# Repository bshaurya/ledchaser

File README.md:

# shauryachaser LED Chaser

a cricket-ball themed LED chaser because why not  
hardware-only, no firmware needed. Powered by a 555 + CD4017  
and mounted inside a shiny 3D-printed cricket ball enclosure

## What is this

Basically I wanted to make something fun, weird, and actually functional.  
So I built an LED chaser circuit (classic 555 + CD4017) and wrapped it inside  
a custom Fusion 360 modeled cricket ball enclosure with seam lines, stitching, and a full LED ring.

## Hardware

- **Logic**: NE555P (clock) + CD4017BE (decade counter)
- **LEDs**: 10x 5mm diffused LEDs arranged around the ball
- **Resistors**: 10x LED current limiters + timing resistors
- **Potentiometer**: 50k trim pot for speed control
- **Caps**: 1uF electrolytic + 0.01uF ceramic
- **Power**: Standard 5V input (2-pin header)
- **Enclosure**: 93mm diameter 3D-printed cricket ball with stitched seam

## How it works

- The **555 timer** generates a square wave clock (rate set by RV1).
- Every clock pulse goes into the **CD4017**, which advances to the next output: Q0 → Q1 → Q2 → ... → Q9 → loops back
- Each Q output drives an LED through a 470Ω resistor.
- Result = lights chase around the seam like a rotating/bouncing cricket ball.

You rotate RV1 to speed up or slow down the chase.

## BOM

**ICs**
- 1x NE555P (DIP-8)
- 1x CD4017BE (DIP-16)

**LEDs**
- 10x 5mm LEDs (any color)

**Resistors**
- 10x 470Ω (LEDs)
- 2x 1kΩ (timing)

**Potentiometer**
- 1x 50kΩ trim pot (3386P style)

**Capacitors**
- 1x 1uF electrolytic
- 1x 0.01uF ceramic

**Connectors**
- 1x 2-pin 2.54mm power header

**PCB**
- 1x Circular 93mm custom PCB (KiCad)

**Case**
- ~70–100g PLA (for the cricket ball halves)
- 4x M3x16 screws (optional if mounting)
- 4x M3 heatset inserts (optional)

## Estimated Prices

(approx retail), see BOM.csv

- LEDs: ~$1.00 for all 10  
- Resistors: ~$0.60  
- NE555P: ~$0.40  
- CD4017BE: ~$0.70  
- Potentiometer: ~$0.50  
- Capacitors: ~$0.25  
- Header: ~$0.10  
- PCB: ~$15 (JLCPCB)  
- PLA: ~$1 worth  
**Total:** ~**$20** all-in

## Building one

- `/ledcha` — KiCad PCB + schematic
- `/cad` — 3D Fusion 360 files for the cricket enclosure
- `/assets` — top/side/bottom views, schema and pcb
Steps:

1. Export Gerbers → order PCB from JLCPCB/Seeed/etc.
2. 3D print the cricket ball halves.
3. Solder the PCB: ICs, resistors, LEDs, pot, caps.
4. Insert the PCB inside the enclosure.
5. Power with 5V.
6. Rotate the pot to change chase speed.

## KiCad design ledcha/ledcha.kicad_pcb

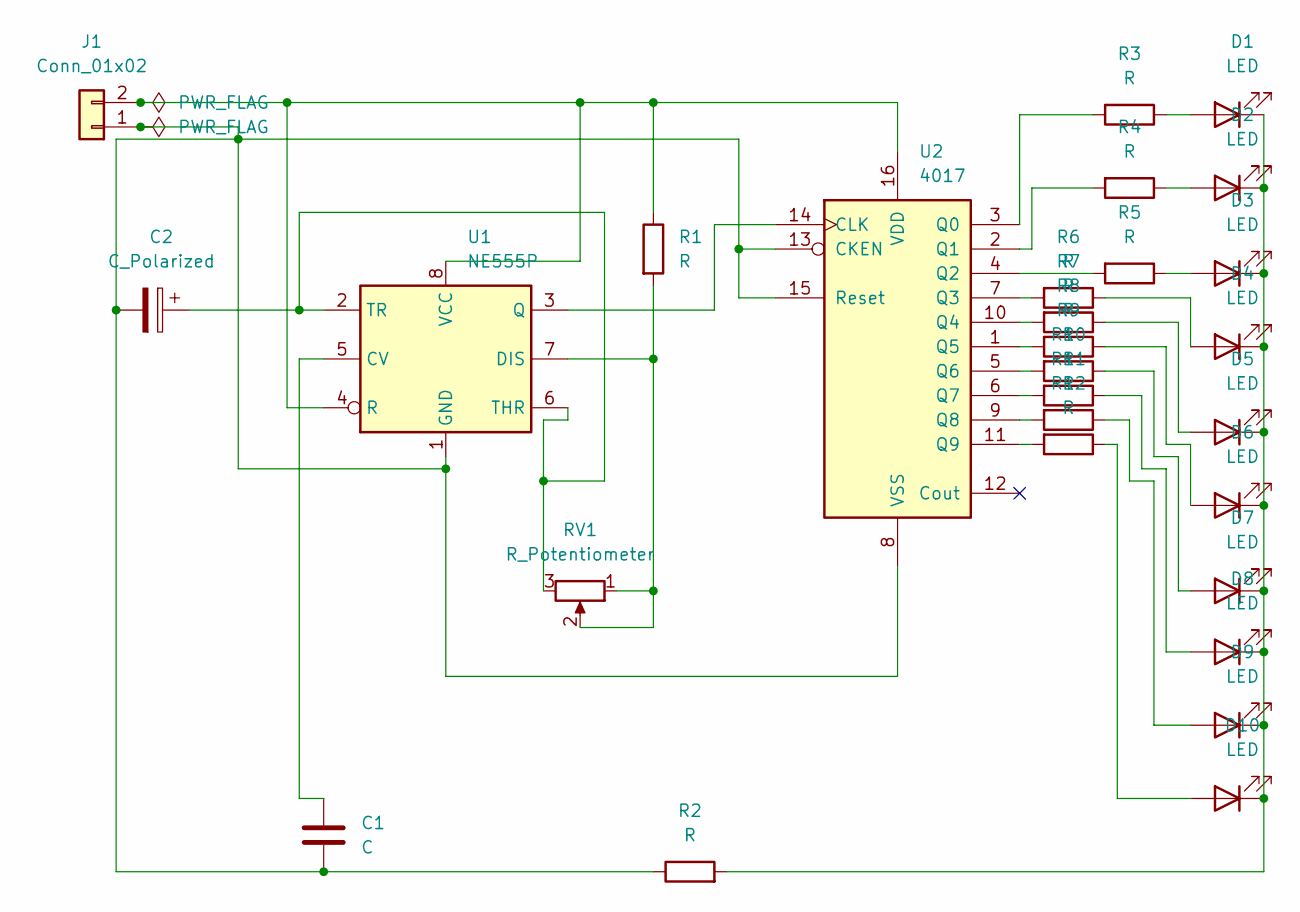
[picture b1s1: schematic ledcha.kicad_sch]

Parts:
C1: C; CP_Radial_D5.0mm_P2.50mm
C2: C_Polarized; C_Disc_D5.0mm_W2.5mm_P2.50mm
D1, D2, D3, D4, D5, D6, D7, D8, D9, D10: LED; LED_D5.0mm
J1: Conn_01x02; PinHeader_1x02_P2.54mm_Vertical
R1, R2, R3, R4, R5, R6, R7, R8, R9, R10, R11, R12: R; R_Axial_DIN0207_L6.3mm_D2.5mm_P7.62mm_Horizontal
RV1: R_Potentiometer; Potentiometer_Bourns_3386P_Vertical
U1: NE555P; DIP-8_W7.62mm
U2: 4017; DIP-16_W7.62mm

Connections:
unnamed: D1.2 (A), R3.1
unnamed: D1.1 (K), D2.1 (K), D3.1 (K), D4.1 (K), D5.1 (K), D6.1 (K), D7.1 (K), D8.1 (K), D9.1 (K), D10.1 (K), R2.2
unnamed: D2.2 (A), R4.1
unnamed: D3.2 (A), R5.1
unnamed: D4.2 (A), R6.1
unnamed: D5.2 (A), R7.1
unnamed: D6.2 (A), R8.1
unnamed: D7.2 (A), R9.1
unnamed: D8.2 (A), R10.1
unnamed: D9.2 (A), R11.1
unnamed: D10.2 (A), R12.1
unnamed: C1.2, C2.2, J1.1, R2.1, U1.1 (GND), U2.8 (VSS), U2.13 (CKEN), U2.15 (Reset)
unnamed: J1.2, R1.1, U1.4 (R), U1.8 (VCC), U2.16 (VDD)
unnamed: C1.1, U1.5 (CV)
unnamed: R1.2, RV1.1, RV1.2, U1.7 (DIS)
unnamed: U1.3 (Q), U2.14 (CLK)
unnamed: C2.1, RV1.3, U1.2 (TR), U1.6 (THR)
unnamed: R3.2, U2.3 (Q0)
unnamed: R4.2, U2.2 (Q1)
unnamed: R5.2, U2.4 (Q2)
unnamed: R6.2, U2.7 (Q3)
unnamed: R7.2, U2.10 (Q4)
unnamed: R8.2, U2.1 (Q5)
unnamed: R9.2, U2.5 (Q6)
unnamed: R10.2, U2.6 (Q7)
unnamed: R11.2, U2.9 (Q8)
unnamed: R12.2, U2.11 (Q9)

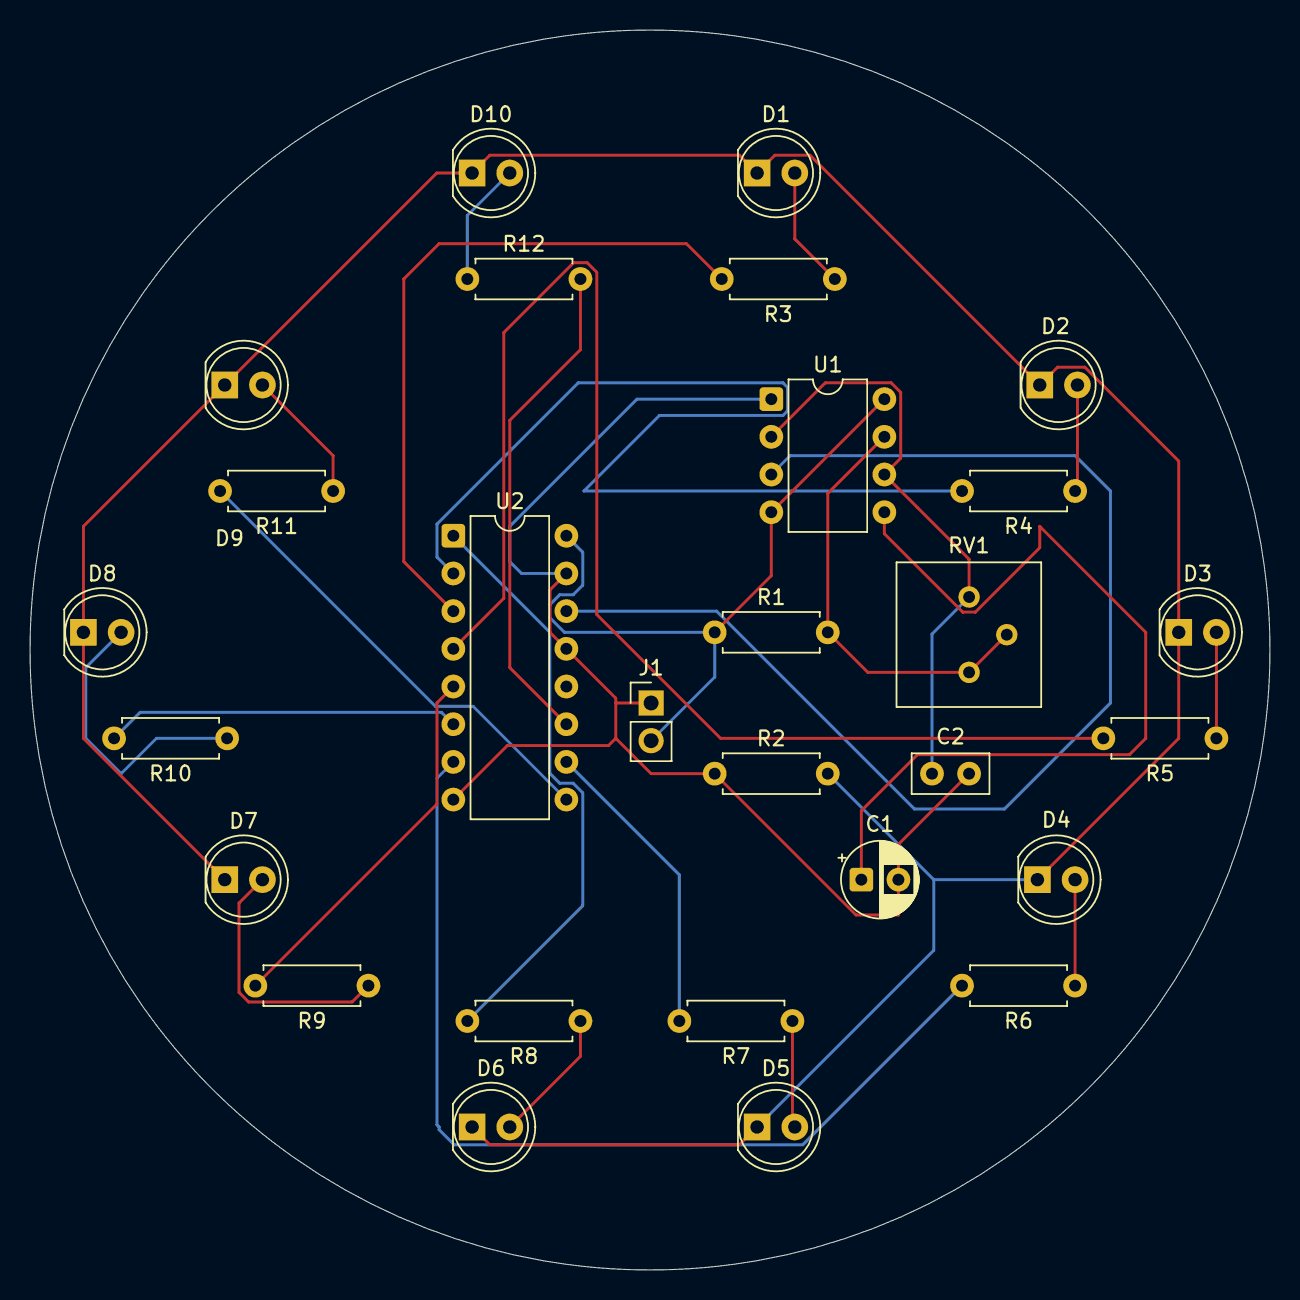
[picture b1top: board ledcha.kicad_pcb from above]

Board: 2 copper layers, 83.6 x 83.6 mm, 28 parts (0 on the bottom side), 27 nets.

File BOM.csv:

Designator,Quantity,Value,Description,Package,Estimated Unit Price (USD),Estimated Total Price (USD)
U1,1,NE555P,555 Timer DIP-8,DIP-8_W7.62mm,0.40,0.40
U2,1,CD4017BE,Decade Counter DIP-16,DIP-16_W7.62mm,0.70,0.70

R1,1,1kΩ,Resistor 1kΩ,Axial 7.62mm,0.05,0.05
R2,1,1kΩ,Resistor 1kΩ,Axial 7.62mm,0.05,0.05
R3,1,470Ω,LED Series Resistor,Axial 7.62mm,0.05,0.05
R4,1,470Ω,LED Series Resistor,Axial 7.62mm,0.05,0.05
R5,1,470Ω,LED Series Resistor,Axial 7.62mm,0.05,0.05
R6,1,470Ω,LED Series Resistor,Axial 7.62mm,0.05,0.05
R7,1,470Ω,LED Series Resistor,Axial 7.62mm,0.05,0.05
R8,1,470Ω,LED Series Resistor,Axial 7.62mm,0.05,0.05
R9,1,470Ω,LED Series Resistor,Axial 7.62mm,0.05,0.05
R10,1,470Ω,LED Series Resistor,Axial 7.62mm,0.05,0.05
R11,1,470Ω,LED Series Resistor,Axial 7.62mm,0.05,0.05
R12,1,470Ω,LED Series Resistor,Axial 7.62mm,0.05,0.05

RV1,1,50kΩ Potentiometer,Adjustable Potentiometer,3386P Vertical,0.50,0.50

C1,1,0.01uF,Non-Polarized Ceramic Capacitor,Disc 5mm,0.10,0.10
C2,1,1uF,Electrolytic Capacitor,Radial 5mm,0.15,0.15

D1,1,LED,Standard 5mm LED,LED_D5.0mm,0.10,0.10
D2,1,LED,Standard 5mm LED,LED_D5.0mm,0.10,0.10
D3,1,LED,Standard 5mm LED,LED_D5.0mm,0.10,0.10
D4,1,LED,Standard 5mm LED,LED_D5.0mm,0.10,0.10
D5,1,LED,Standard 5mm LED,LED_D5.0mm,0.10,0.10
D6,1,LED,Standard 5mm LED,LED_D5.0mm,0.10,0.10
D7,1,LED,Standard 5mm LED,LED_D5.0mm,0.10,0.10
D8,1,LED,Standard 5mm LED,LED_D5.0mm,0.10,0.10
D9,1,LED,Standard 5mm LED,LED_D5.0mm,0.10,0.10
D10,1,LED,Standard 5mm LED,LED_D5.0mm,0.10,0.10

J1,1,2-pin Header,Power Connector,PinHeader_1x02_P2.54mm,0.10,0.10

PCB,1,93mm Diameter Round PCB,Custom Board,N/A,15.98,15.98

TOTAL,, , , , ,,
TOTAL_COMPONENT_COST,,, , , ,3.65
TOTAL_WITH_PCB,,, , , ,19.63

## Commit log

2025-11-23 initial
2025-11-24 uploaded all files
2025-11-24 added .step file for cad
2025-11-24 fixed bom
